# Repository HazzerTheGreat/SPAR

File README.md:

# SPAR

This is a flight controller primarily designed for fixed wing aircraft (or quadcopters etc) that is designed to 
run either BetaFlight, INAV or ArduPilot firmware. It handles flight stabilization, OSD, control of servos, waypoints,
data logging and anything else any other flight controller can do. This flight controller has an STM32H743 which is 
an extremely capable MCU with a blazing fast speed of up to 480MHz. Most likely overkill for the majority of applications
but it can accomodate for the most demanding projects. I made it as I was interested in the design of such systems
and also enjoy building aircraft and could find a highly capable flight controller useful plus the benefit that I have
built it myself.

**Specs:**

- ICM-42688-P for peak performance and high resolution positional sensing
- STM32H743 for processing whatever you need
- 5V and 9V buck converters for handling high power peripherals
- Micro SD card for black box logging
- 4 in 1 ESC support with DSHOT
- 6 other PWM outputs
- Analog OSD through AT7456E
- Support for external magnetometer, airspeed sensor and GPS
- BMP280 barometer for altitude measurements

**Peripherals:**

The flight controller board has connectors for external airspeed, GPS, and mag sensors as well as plugs for ELRS, 4 in 1 ESC, analog camera, analog VTX, digital VTX and PWM LEDs.

**Firmware/flashing:**

This board does not have custom firmware, it is based on INAV: https://github.com/iNavFlight/inav/.
However a custom build of INAV including relevant target configuration is required.
I will put this custom target in the /Project_Files/INAV folder. This tutorial shows how to build INAV with a custom target: https://youtu.be/ThrsS_y9zDo?si=cllAaaTRHZ6ADbW4
To flash the board, the board must be powered up with the boot0 pin shorted to enter DFU mode on the STM32 where it can then be flashed in INAV configurator.

**BOM:**

The board costs about £27 from JLCPCB for a basic 6 layer PCB. The BOM for components can be found in the BOM.csv in the production folder. This totals around £40 which mainly
accounts for buying large quantities of passives so the per board price is probably much cheaper.

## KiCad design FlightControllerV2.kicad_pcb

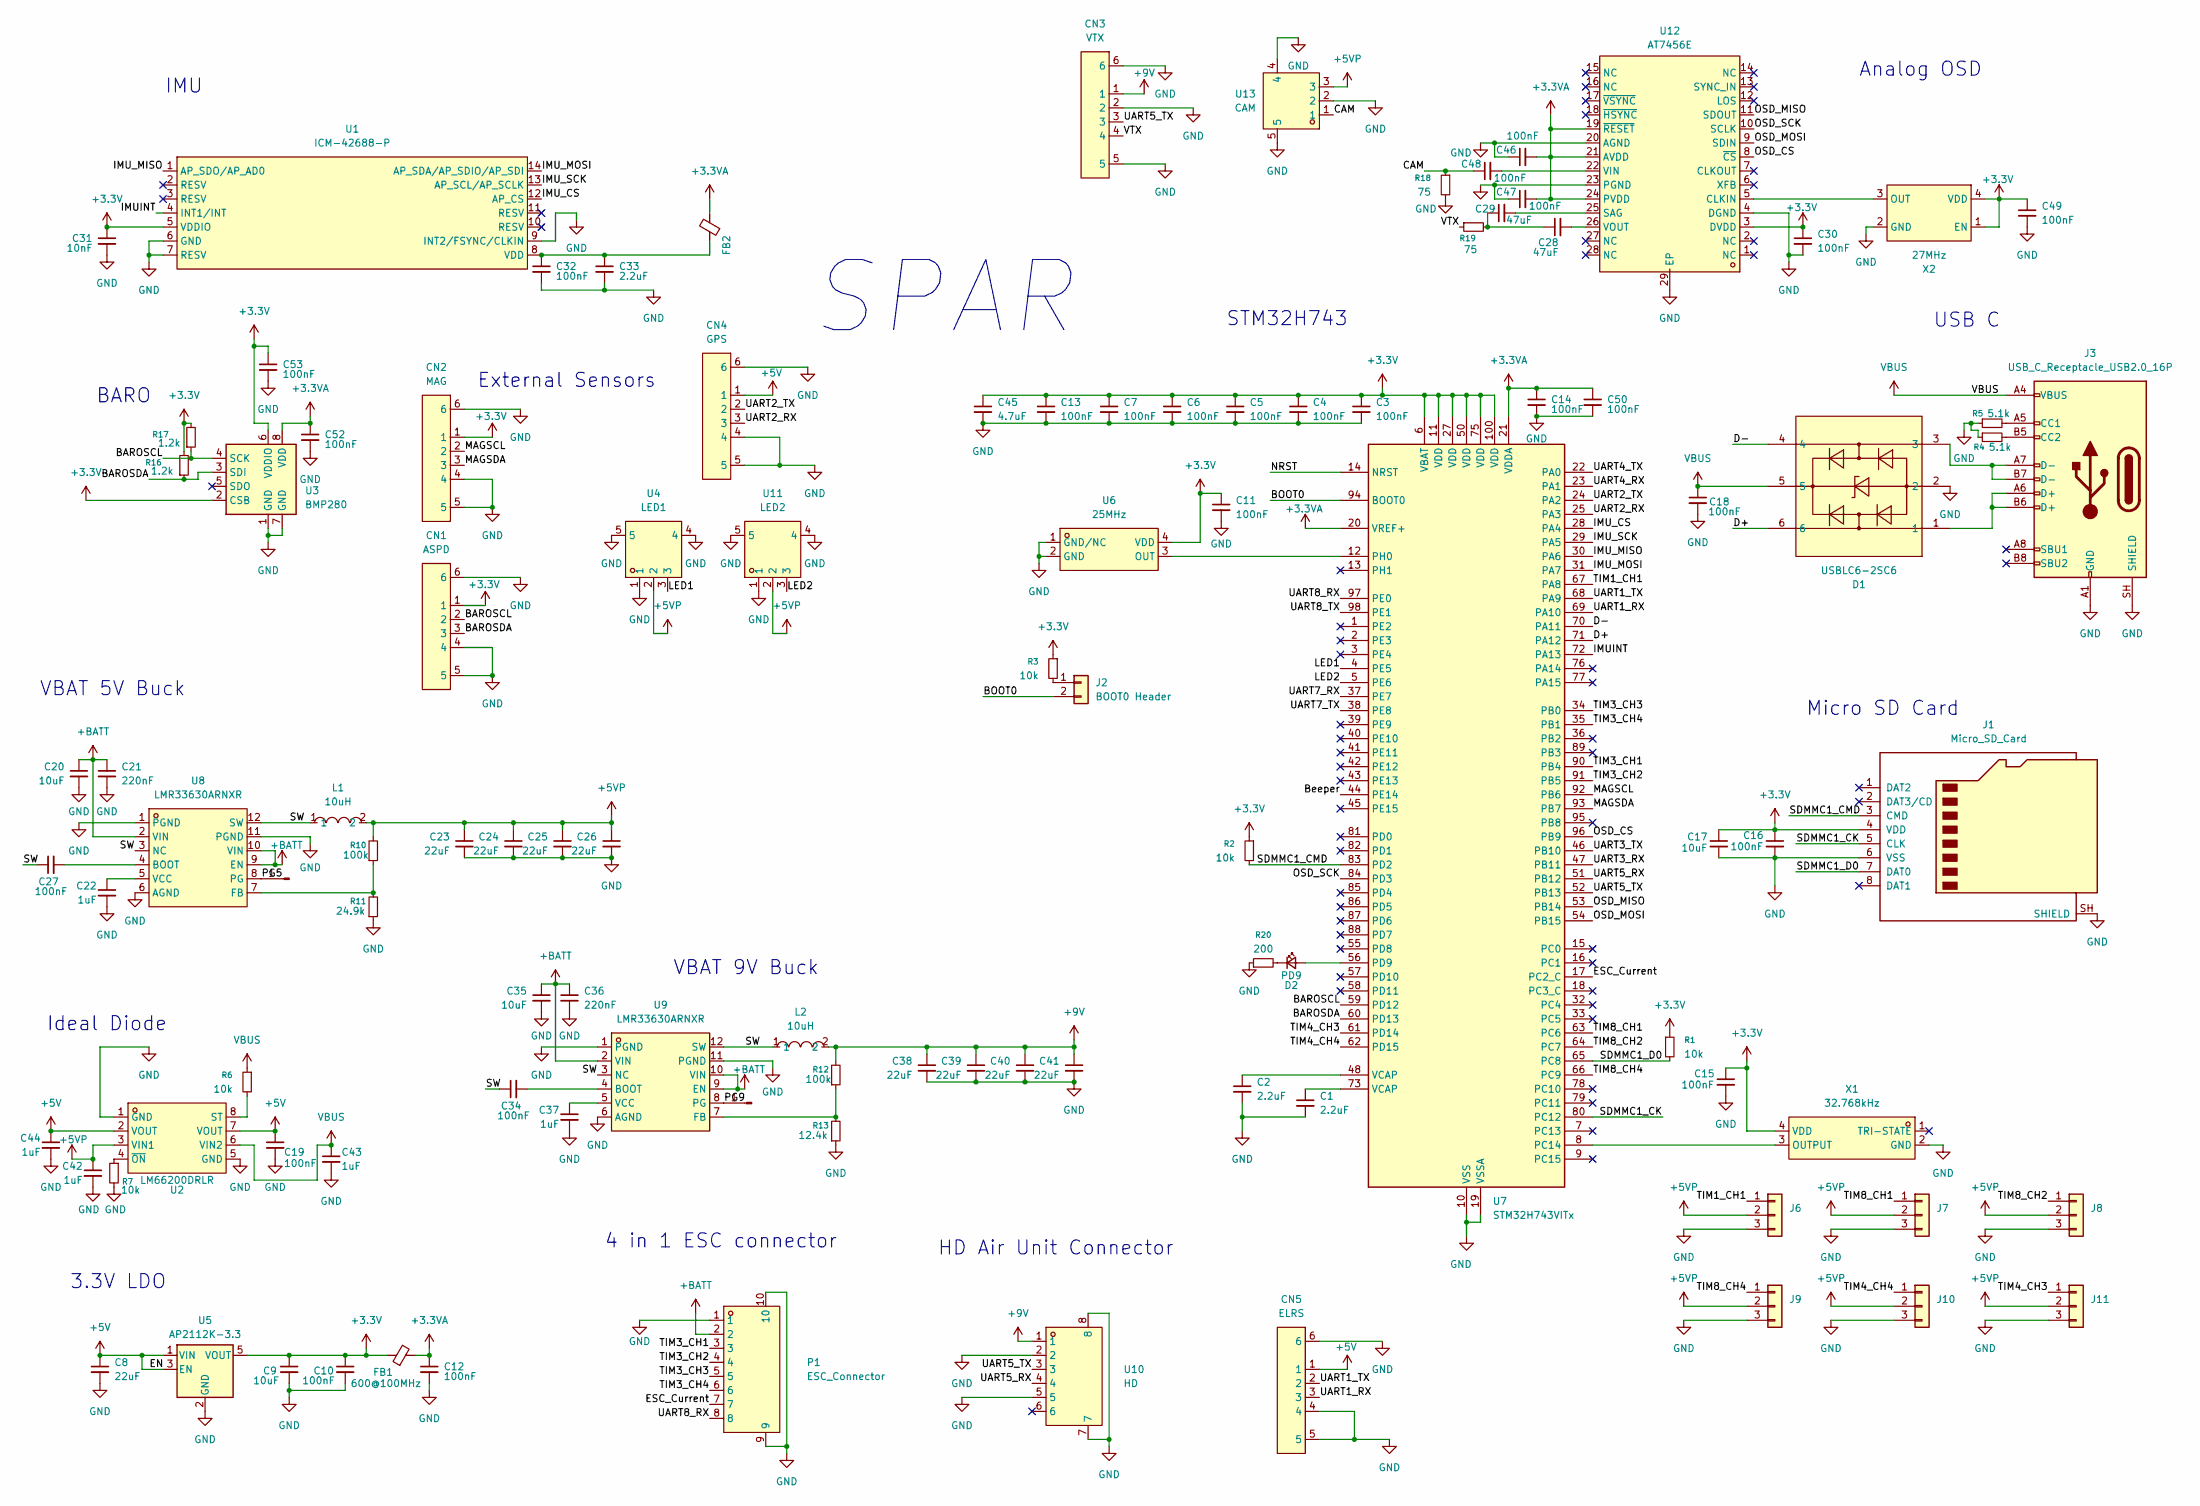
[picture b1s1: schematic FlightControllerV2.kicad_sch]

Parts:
C1, C2, C33: 2.2uF; C_0402_1005Metric
C3, C4, C5, C6, C7, C10, C11, C12, C13, C14, C15, C16, C18, C19, C27, C30, C32, C34, C46, C47, C48, C49, C50, C52, C53: 100nF; C_0402_1005Metric
C8, C23, C24, C25, C26, C38, C39, C40, C41: 22uF; C_0603_1608Metric
C9, C17, C20, C35: 10uF; C_0402_1005Metric
C21, C36: 220nF; C_0402_1005Metric
C22, C37, C42, C43, C44: 1uF; C_0402_1005Metric
C28, C29: 47uF; C_0603_1608Metric
C31: 10nF; C_0402_1005Metric
C45: 4.7uF; C_0402_1005Metric
CN1: ASPD; CONN-SMD_4P-P1.00_SM04B-SRSS-TB-LF-SN; MPN SM04B-SRSS-TB(LF)(SN); LCSC Part C160404
CN2: MAG; CONN-SMD_4P-P1.00_SM04B-SRSS-TB-LF-SN; MPN SM04B-SRSS-TB(LF)(SN); LCSC Part C160404
CN3: VTX; CONN-SMD_4P-P1.00_SM04B-SRSS-TB-LF-SN; MPN SM04B-SRSS-TB(LF)(SN); LCSC Part C160404
CN4: GPS; CONN-SMD_4P-P1.00_SM04B-SRSS-TB-LF-SN; MPN SM04B-SRSS-TB(LF)(SN); LCSC Part C160404
CN5: ELRS; CONN-SMD_4P-P1.00_SM04B-SRSS-TB-LF-SN; MPN SM04B-SRSS-TB(LF)(SN); LCSC Part C160404
D1: USBLC6-2SC6; SOT-23-6_L2.9-W1.6-P0.95-LS2.8-BL; MPN USBLC6-2SC6; LCSC Part C7519
D2: PD9; LED_0603_1608Metric
FB1, FB2: 600@100MHz; C_0603_1608Metric
J1: Micro_SD_Card; TF-SMD_TF-PUSH
J2: BOOT0 Header; PinHeader_1x02_P2.54mm_Vertical
J3: USB_C_Receptacle_USB2.0_16P; USB-C-SMD_TYPE-C-16PIN-2MD-073
J4, J5: Conn_01x01_Pin
J6, J7, J8, J9, J10, J11: Conn_01x03; PinHeader_1x03_P2.54mm_Vertical
L1, L2: 10uH; IND-SMD_L5.2-W5.2_MCW-0530; MPN SMMS0530-100M; LCSC Part C181721
P1: ESC_Connector; CONN-TH_SM08B-SRSS-TB-LF-SN; MPN SM08B-SRSS-TB(LF)(SN); LCSC Part C160407
R1, R2, R3, R6, R7: 10k; R_0603_1608Metric
R4, R5: 5.1k; R_0603_1608Metric
R10, R12: 100k; R_0603_1608Metric
R11: 24.9k; R_0603_1608Metric
R13: 12.4k; R_0603_1608Metric
R16, R17: 1.2k; R_0603_1608Metric
R18, R19: 75; R_0603_1608Metric
R20: 200; R_0603_1608Metric
U1: ICM-42688-P; LGA-14_L3.0-W2.5-P0.50-TL; MPN ICM-42688-P; LCSC Part C1850418
U2: LM66200DRLR; SOT-583-8_L2.1-W1.2-P0.50-LS1.6-BL; MPN LM66200DRLR; LCSC Part C3235556
U3: BMP280; Bosch_LGA-8_2x2.5mm_P0.65mm_ClockwisePinNumbering
U4: LED1; CONN-SMD_SM03B-SRSS-TB-LF-SN-P; MPN SM03B-SRSS-TB(LF)(SN); LCSC Part C160403
U5: AP2112K-3.3; SOT-23-5
U6: 25MHz; OSC-SMD_4P-L2.5-W2.0-BL; MPN 8122S-25.000NQ33FTL; LCSC Part C20623084
U7: STM32H743VITx; LQFP-100_14x14mm_P0.5mm
U8, U9: LMR33630ARNXR; VQFN-12_L3.0-W2.0-P0.65-BL_TI_RNX; MPN LMR33630ARNXR; LCSC Part C2861505
U10: HD; CONN-SMD_SM06B-SRSS-TB-LF-SN; MPN SM06B-SRSS-TB(LF)(SN); LCSC Part C160405
U11: LED2; CONN-SMD_SM03B-SRSS-TB-LF-SN-P; MPN SM03B-SRSS-TB(LF)(SN); LCSC Part C160403
U12: AT7456E; TSSOP-28_L9.7-W4.4-P0.65-LS6.4-BL-EP-2; MPN AT7456E; LCSC Part C82351
U13: CAM; CONN-SMD_SM03B-SRSS-TB-LF-SN-P; MPN SM03B-SRSS-TB(LF)(SN); LCSC Part C160403
X1: 32.768kHz; OSC-SMD_4P-L3.2-W2.5-BL; MPN SX3M32.768KM20F30TNN; LCSC Part C2901582
X2: 27MHz; OSC-SMD_4P-L3.2-W2.5-BL; MPN SX3M27.000M20F30TNN; LCSC Part C2901577

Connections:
+3.3V: C3.1, C4.1, C5.1, C6.1, C7.1, C9.1, C10.1, C11.1, C13.1, C15.1, C16.1, C17.1, C30.1, C31.1, C45.1, C49.1, C53.1, CN1.1, CN2.1, FB1.1, J1.4 (VDD), R1.1, R2.1, R3.1, R16.2, R17.2, U1.5 (VDDIO), U3.2 (CSB), U3.6 (VDDIO), U5.5 (VOUT), U6.4 (VDD), U7.6 (VBAT), U7.11 (VDD), U7.27 (VDD), U7.50 (VDD), U7.75 (VDD), U7.100 (VDD), U12.3 (DVDD), X1.4 (VDD), X2.1 (EN), X2.4 (VDD)
+3.3VA: C12.1, C14.1, C46.2, C47.2, C50.1, C52.1, FB1.2, FB2.2, U3.8 (VDD), U7.20 (VREF+), U7.21 (VDDA), U12.19 (~RESET), U12.21 (AVDD), U12.24 (PVDD)
+5V: C8.1, C19.1, C44.1, CN4.1, CN5.1, U2.2 (VOUT), U2.7 (VOUT), U5.1 (VIN), U5.3 (EN)
+5VP: C23.1, C24.1, C25.1, C26.1, C42.1, J6.2, J7.2, J8.2, J9.2, J10.2, J11.2, L1.2, R10.2, U2.3 (VIN1), U4.2, U11.2, U13.3
+9V: C38.1, C39.1, C40.1, C41.1, CN3.1, L2.2, R12.2, U10.1
+BATT: C20.1, C21.1, C35.1, C36.1, P1.2, U8.2 (VIN), U8.9 (EN), U8.10 (VIN), U9.2 (VIN), U9.9 (EN), U9.10 (VIN)
/BAROSCL: CN1.2, R17.1, U3.4 (SCK), U7.59 (PD12)
/BAROSDA: CN1.3, R16.1, U3.3 (SDI), U7.60 (PD13)
/BOOT0: J2.2, U7.94 (BOOT0)
/Beeper: U7.44 (PE14)
/CAM: C48.1, R18.1, U13.1
/D+: D1.6, U7.71 (PA12)
/D-: D1.4, U7.70 (PA11)
/ESC_Current: P1.7, U7.17 (PC2_C)
/IMUINT: U1.4 (INT1/INT), U7.72 (PA13)
/IMU_CS: U1.12 (AP_CS), U7.28 (PA4)
/IMU_MISO: U1.1 (AP_SDO/AP_AD0), U7.30 (PA6)
/IMU_MOSI: U1.14 (AP_SDA/AP_SDIO/AP_SDI), U7.31 (PA7)
/IMU_SCK: U1.13 (AP_SCL/AP_SCLK), U7.29 (PA5)
/LED1: U4.3, U7.4 (PE5)
/LED2: U7.5 (PE6), U11.3
/MAGSCL: CN2.2, U7.92 (PB6)
/MAGSDA: CN2.3, U7.93 (PB7)
/NRST: U7.14 (NRST)
/OSD_CS: U7.96 (PB9), U12.8 (~CS)
/OSD_MISO: U7.53 (PB14), U12.11 (SDOUT)
/OSD_MOSI: U7.54 (PB15), U12.9 (SDIN)
/OSD_SCK: U7.84 (PD3), U12.10 (SCLK)
/PG5: J4.1, U8.8 (PG)
/PG9: J5.1, U9.8 (PG)
/SDMMC1_CK: J1.5 (CLK), U7.80 (PC12)
/SDMMC1_CMD: J1.3 (CMD), R2.2, U7.83 (PD2)
/SDMMC1_D0: J1.7 (DAT0), R1.2, U7.65 (PC8)
/SW: C27.1, C34.1, L1.1, L2.1, U8.3 (NC), U8.12 (SW), U9.3 (NC), U9.12 (SW)
/TIM1_CH1: J6.1, U7.67 (PA8)
/TIM3_CH1: P1.3, U7.90 (PB4)
/TIM3_CH2: P1.4, U7.91 (PB5)
/TIM3_CH3: P1.5, U7.34 (PB0)
/TIM3_CH4: P1.6, U7.35 (PB1)
/TIM4_CH3: J11.1, U7.61 (PD14)
/TIM4_CH4: J10.1, U7.62 (PD15)
/TIM8_CH1: J7.1, U7.63 (PC6)
/TIM8_CH2: J8.1, U7.64 (PC7)
/TIM8_CH4: J9.1, U7.66 (PC9)
/UART1_RX: CN5.3, U7.69 (PA10)
/UART1_TX: CN5.2, U7.68 (PA9)
/UART2_RX: CN4.3, U7.25 (PA3)
/UART2_TX: CN4.2, U7.24 (PA2)
/UART3_RX: U7.47 (PB11)
/UART3_TX: U7.46 (PB10)
/UART4_RX: U7.23 (PA1)
/UART4_TX: U7.22 (PA0)
/UART5_RX: U7.51 (PB12), U10.4
/UART5_TX: CN3.3, U7.52 (PB13), U10.3
/UART7_RX: U7.37 (PE7)
/UART7_TX: U7.38 (PE8)
/UART8_RX: P1.8, U7.97 (PE0)
/UART8_TX: U7.98 (PE1)
/VTX: CN3.4, R19.1
GND: C1.2, C2.2, C3.2, C4.2, C5.2, C6.2, C7.2, C8.2, C9.2, C10.2, C11.2, C12.2, C13.2, C14.2, C15.2, C16.2, C17.2, C18.2, C19.2, C20.2, C21.2, C22.2, C23.2, C24.2, C25.2, C26.2, C30.2, C31.2, C32.2, C33.2, C35.2, C36.2, C37.2, C38.2, C39.2, C40.2, C41.2, C42.2, C43.2, C44.2, C45.2, C46.1, C47.1, C49.2, C50.2, C52.2, C53.2, CN1.4, CN1.5, CN1.6, CN2.4, CN2.5, CN2.6, CN3.2, CN3.5, CN3.6, CN4.4, CN4.5, CN4.6, CN5.4, CN5.5, CN5.6, D1.2, J1.6 (VSS), J1.SH (SHIELD), J3.13, J3.14, J3.A1 (GND), J3.A1B12, J3.A12 (GND), J3.B1 (GND), J3.B1A12, J3.B12 (GND), J3.SH (SHIELD), J6.3, J7.3, J8.3, J9.3, J10.3, J11.3, P1.1, P1.9, P1.10, R4.1, R5.1, R7.2, R11.1, R13.1, R18.2, R20.1, U1.6 (GND), U1.7 (RESV), U1.9 (INT2/FSYNC/CLKIN), U2.1 (GND), U2.5 (GND), U3.1 (GND), U3.7 (GND), U4.1, U4.4, U4.5, U5.2 (GND), U6.1 (GND/NC), U6.2 (GND), U7.10 (VSS), U7.19 (VSSA), U7.26 (VSS), U7.49 (VSS), U7.74 (VSS), U7.99 (VSS), U8.1 (PGND), U8.6 (AGND), U8.11 (PGND), U9.1 (PGND), U9.6 (AGND), U9.11 (PGND), U10.2, U10.5, U10.7, U10.8, U11.1, U11.4, U11.5, U12.4 (DGND), U12.20 (AGND), U12.23 (PGND), U12.29 (EP), U13.2, U13.4, U13.5, X1.2 (GND), X2.2 (GND)
unnamed: C1.1, U7.73 (VCAP)
unnamed: C2.1, U7.48 (VCAP)
unnamed: C28.1, C29.1, R19.2
unnamed: D1.1, J3.A6 (D+), J3.B6 (D+)
unnamed: D1.3, J3.A7 (D-), J3.B7 (D-)
unnamed: D2.2 (A), U7.56 (PD9)
unnamed: D2.1 (K), R20.2
unnamed: J2.1, R3.2
unnamed: J3.A5 (CC1), R5.2
unnamed: J3.B5 (CC2), R4.2
unnamed: C32.1, C33.1, FB2.1, U1.8 (VDD)
unnamed: R6.2, U2.8 (ST)
unnamed: R7.1, U2.4 (~ON)
unnamed: U6.3 (OUT), U7.12 (PH0)
unnamed: U7.8 (PC14), X1.3 (OUTPUT)
unnamed: C27.2, U8.4 (BOOT)
unnamed: R10.1, R11.2, U8.7 (FB)
unnamed: C22.1, U8.5 (VCC)
unnamed: C34.2, U9.4 (BOOT)
unnamed: R12.1, R13.2, U9.7 (FB)
unnamed: C37.1, U9.5 (VCC)
unnamed: U12.5 (CLKIN), X2.3 (OUT)
unnamed: C29.2, U12.25 (SAG)
unnamed: C48.2, U12.22 (VIN)
unnamed: C28.2, U12.26 (VOUT)
VBUS: C18.1, C43.1, D1.5, J3.A4 (VBUS), J3.A9 (VBUS), J3.B4 (VBUS), J3.B9 (VBUS), R6.1, U2.6 (VIN2)

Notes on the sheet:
External Sensors
Analog OSD
BARO
Ideal Diode
SPAR
VBAT 5V Buck
VBAT 9V Buck
Micro SD Card
4 in 1 ESC connector
IMU
3.3V LDO
STM32H743
USB C
HD Air Unit Connector

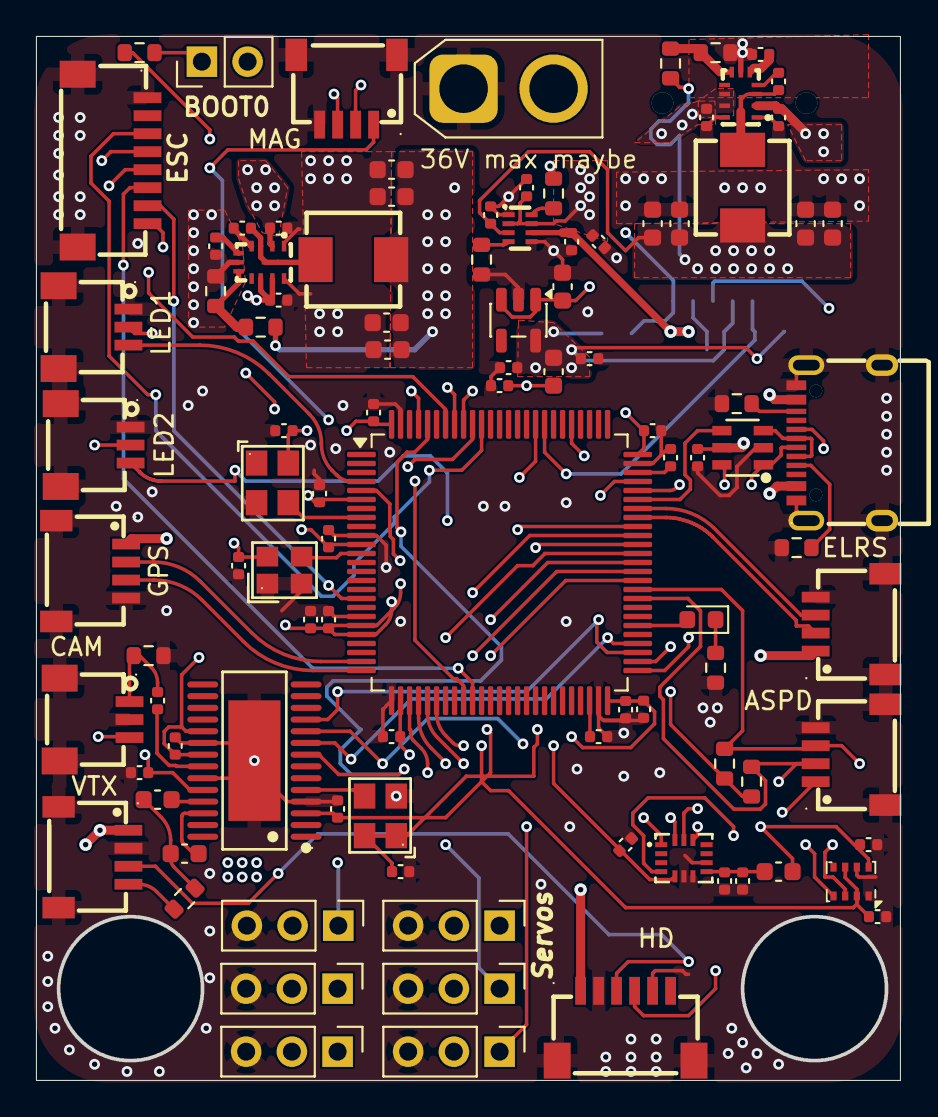
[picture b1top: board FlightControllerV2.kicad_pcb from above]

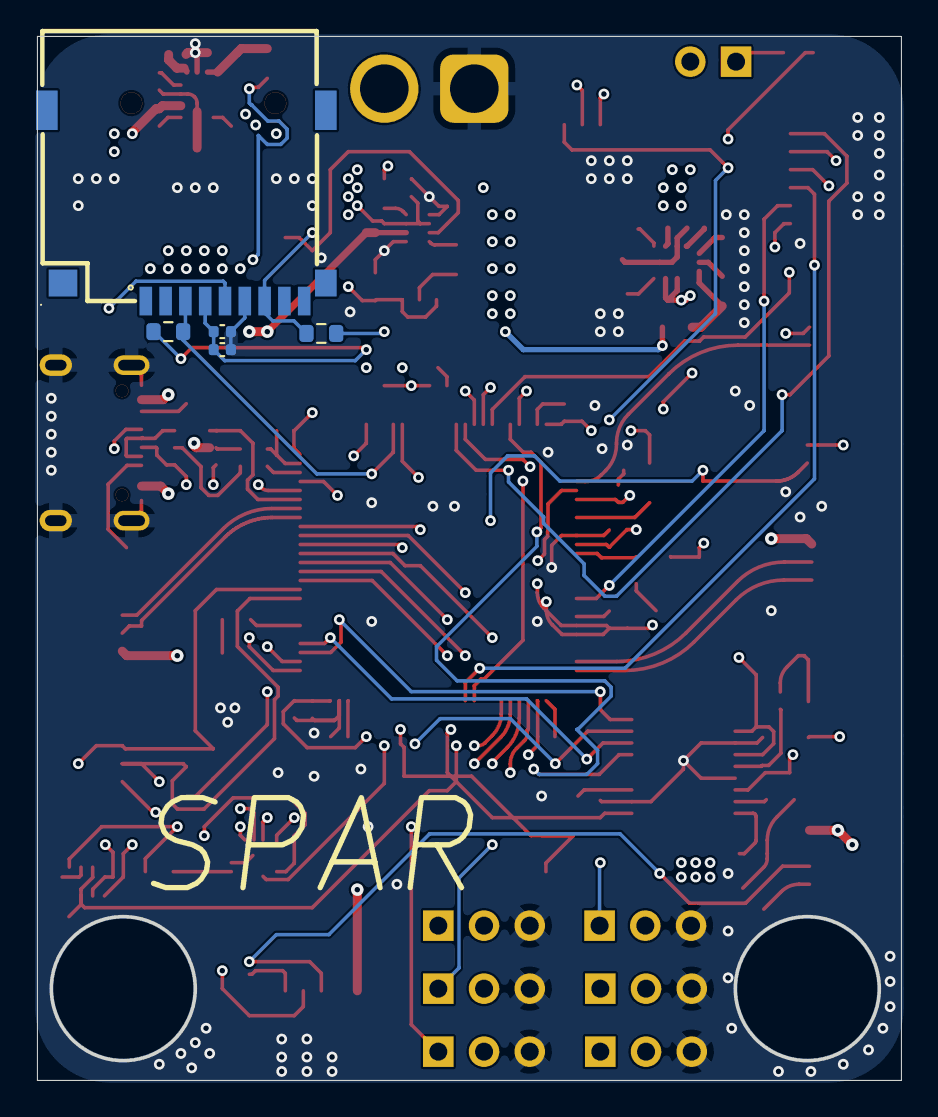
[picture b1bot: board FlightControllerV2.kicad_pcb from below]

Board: 6 copper layers, 48.0 x 58.0 mm, 104 parts (5 on the bottom side), 75 nets.

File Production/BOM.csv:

Reference,Qty,Value,DNP,Exclude from BOM,Exclude from Board,Exclude from Simulation,Exclude from Position Files,Footprint,Datasheet,,,,,,,Price (minimum order):,
"C1,C2,C33",3,2.2uF,,,,,${EXCLUDE_FROM_POS_FILES},Capacitor_SMD:C_0402_1005Metric,,,,,,,,,0.45
"C3,C4,C5,C6,C7,C10,C11,C12,C13,C14,C15,C16,C18,C19,C27,C30,C32,C34,C46,C47,C48,C49,C50,C52,C53",25,100nF,,,,,${EXCLUDE_FROM_POS_FILES},Capacitor_SMD:C_0402_1005Metric,,,,,,,,,0.45
"C8,C23,C24,C25,C26,C38,C39,C40,C41",9,22uF,,,,,${EXCLUDE_FROM_POS_FILES},Capacitor_SMD:C_0603_1608Metric,,,,,,,,,0.45
"C9,C17,C20,C35",4,10uF,,,,,${EXCLUDE_FROM_POS_FILES},Capacitor_SMD:C_0402_1005Metric,,,,,,,,,0.45
"C21,C36",2,220nF,,,,,${EXCLUDE_FROM_POS_FILES},Capacitor_SMD:C_0402_1005Metric,,,,,,,,,0.45
"C22,C37,C42,C43,C44",5,1uF,,,,,${EXCLUDE_FROM_POS_FILES},Capacitor_SMD:C_0402_1005Metric,,,,,,,,,0.45
"C28,C29",2,47uF,,,,,${EXCLUDE_FROM_POS_FILES},Capacitor_SMD:C_0603_1608Metric,,,,,,,,,0.97
C31,1,10nF,,,,,${EXCLUDE_FROM_POS_FILES},Capacitor_SMD:C_0402_1005Metric,,,,,,,,,0.45
C45,1,4.7uF,,,,,${EXCLUDE_FROM_POS_FILES},Capacitor_SMD:C_0402_1005Metric,,,,,,,,,0.45
CN1,1,ASPD,,,,,${EXCLUDE_FROM_POS_FILES},easyeda2kicad:CONN-SMD_4P-P1.00_SM04B-SRSS-TB-LF-SN,https://lcsc.com/product-detail/Others_JST-Sales-America__JS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,,,,,,,,0.18
CN2,1,MAG,,,,,${EXCLUDE_FROM_POS_FILES},easyeda2kicad:CONN-SMD_4P-P1.00_SM04B-SRSS-TB-LF-SN,https://lcsc.com/product-detail/Others_JST-Sales-America__JS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,,,,,,,,0.19
CN3,1,VTX,,,,,${EXCLUDE_FROM_POS_FILES},easyeda2kicad:CONN-SMD_4P-P1.00_SM04B-SRSS-TB-LF-SN,https://lcsc.com/product-detail/Others_JST-Sales-America__JS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,,,,,,,,0.18
CN4,1,GPS,,,,,${EXCLUDE_FROM_POS_FILES},easyeda2kicad:CONN-SMD_4P-P1.00_SM04B-SRSS-TB-LF-SN,https://lcsc.com/product-detail/Others_JST-Sales-America__JS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,,,,,,,,0.18
CN5,1,ELRS,,,,,${EXCLUDE_FROM_POS_FILES},easyeda2kicad:CONN-SMD_4P-P1.00_SM04B-SRSS-TB-LF-SN,https://lcsc.com/product-detail/Others_JST-Sales-America__JS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,,,,,,,,0.18
D1,1,USBLC6-2SC6,,,,,${EXCLUDE_FROM_POS_FILES},easyeda2kicad:SOT-23-6_L2.9-W1.6-P0.95-LS2.8-BL,https://lcsc.com/product-detail/Diodes-ESD_STMicroelectronic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,,,,,,,,0.82
D2,1,PD9,,,,,${EXCLUDE_FROM_POS_FILES},LED_SMD:LED_0603_1608Metric,,,,,,,,,0.78
"FB1,FB2",2,600@100MHz,,,,,${EXCLUDE_FROM_POS_FILES},Capacitor_SMD:C_0603_1608Metric,,,,,,,,,0.79
J1,1,Micro_SD_Card,,,,,${EXCLUDE_FROM_POS_FILES},easyeda2kicad:TF-SMD_TF-PUSH,https://www.we-online.com/components/products/datasheet/6930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,,,,,,,,0.56
J2,1,BOOT0 Header,,,,,${EXCLUDE_FROM_POS_FILES},Connector_PinHeader_2.54mm:PinHeader_1x02_P2.54mm_Vertical,,,,,,,,,0.12
J3,1,USB_C_Receptacle_USB2.0_16P,,,,,${EXCLUDE_FROM_POS_FILES},easyeda2kicad:USB-C-SMD_TYPE-C-16PIN-2MD-073,https://www.usb.org/sites/default/files/documents/usb_type-c.zip,,,,,,,,1.27
"J4,J5",2,Conn_01x01_Pin,,,,,${EXCLUDE_FROM_POS_FILES},,,,,,,,,,0.2
"J6,J7,J8,J9,J10,J11",6,Conn_01x03,,,,,${EXCLUDE_FROM_POS_FILES},Connector_PinHeader_2.54mm:PinHeader_1x03_P2.54mm_Vertical,,,,,,,,,0.8
"L1,L2",2,10uH,,,,,${EXCLUDE_FROM_POS_FILES},easyeda2kicad:IND-SMD_L5.2-W5.2_MCW-0530,https://lcsc.com/product-detail/Power-Inductors_10uH-20_C181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,,,,,,,,0.7
P1,1,ESC_Connector,,,,,${EXCLUDE_FROM_POS_FILES},easyeda2kicad:CONN-TH_SM08B-SRSS-TB-LF-SN,https://lcsc.com/product-detail/Others_JST-Sales-America__JS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,,,,,,,,0.55
"R1,R2,R3,R6,R7",5,10k,,,,,${EXCLUDE_FROM_POS_FILES},Resistor_SMD:R_0603_1608Metric,,,,,,,,,0.45
"R4,R5",2,5.1k,,,,,${EXCLUDE_FROM_POS_FILES},Resistor_SMD:R_0603_1608Metric,,,,,,,,,0.45
"R10,R12",2,100k,,,,,${EXCLUDE_FROM_POS_FILES},Resistor_SMD:R_0603_1608Metric,,,,,,,,,0.45
R11,1,24.9k,,,,,${EXCLUDE_FROM_POS_FILES},Resistor_SMD:R_0603_1608Metric,,,,,,,,,0.45
R13,1,12.4k,,,,,${EXCLUDE_FROM_POS_FILES},Resistor_SMD:R_0603_1608Metric,,,,,,,,,0.45
"R16,R17",2,1.2k,,,,,${EXCLUDE_FROM_POS_FILES},Resistor_SMD:R_0603_1608Metric,,,,,,,,,0.45
"R18,R19",2,75,,,,,${EXCLUDE_FROM_POS_FILES},Resistor_SMD:R_0603_1608Metric,,,,,,,,,0.45
R20,1,200,,,,,${EXCLUDE_FROM_POS_FILES},Resistor_SMD:R_0603_1608Metric,,,,,,,,,0.45
U1,1,ICM-42688-P,,,,,${EXCLUDE_FROM_POS_FILES},easyeda2kicad:LGA-14_L3.0-W2.5-P0.50-TL,https://www.lcsc.com/datasheet/C1850418.pdf,,,,,,,,6.29
U2,1,LM66200DRLR,,,,,${EXCLUDE_FROM_POS_FILES},easyeda2kicad:SOT-583-8_L2.1-W1.2-P0.50-LS1.6-BL,https://www.lcsc.com/datasheet/C3235556.pdf,,,,,,,,0.53
U3,1,BMP280,,,,,${EXCLUDE_FROM_POS_FILES},Package_LGA:Bosch_LGA-8_2x2.5mm_P0.65mm_ClockwisePinNumbering,https://ae-bst.resource.bosch.com/media/_tech/media/datashee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,,,,,,,,1
U4,1,LED1,,,,,${EXCLUDE_FROM_POS_FILES},easyeda2kicad:CONN-SMD_SM03B-SRSS-TB-LF-SN-P,https://lcsc.com/product-detail/Others_JST-Sales-America__JS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,,,,,,,,0.33
U5,1,AP2112K-3.3,,,,,${EXCLUDE_FROM_POS_FILES},Package_TO_SOT_SMD:SOT-23-5,https://www.diodes.com/assets/Datasheets/AP2112.pdf,,,,,,,,0.24
U6,1,25MHz,,,,,${EXCLUDE_FROM_POS_FILES},easyeda2kicad:OSC-SMD_4P-L2.5-W2.0-BL,https://www.lcsc.com/datasheet/C20623084.pdf,,,,,,,,0.52
U7,1,STM32H743VITx,,,,,${EXCLUDE_FROM_POS_FILES},Package_QFP:LQFP-100_14x14mm_P0.5mm,https://www.st.com/resource/en/datasheet/stm32h743vi.pdf,,,,,,,,10.71
"U8,U9",2,LMR33630ARNXR,,,,,${EXCLUDE_FROM_POS_FILES},easyeda2kicad:VQFN-12_L3.0-W2.0-P0.65-BL_TI_RNX,https://www.lcsc.com/datasheet/C2861505.pdf,,,,,,,,3.64
U10,1,HD,,,,,${EXCLUDE_FROM_POS_FILES},easyeda2kicad:CONN-SMD_SM06B-SRSS-TB-LF-SN,https://lcsc.com/product-detail/Others_JST-Sales-America__JS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,,,,,,,,0.7
U11,1,LED2,,,,,${EXCLUDE_FROM_POS_FILES},easyeda2kicad:CONN-SMD_SM03B-SRSS-TB-LF-SN-P,https://lcsc.com/product-detail/Others_JST-Sales-America__JS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,,,,,,,,0.6
U12,1,AT7456E,,,,,${EXCLUDE_FROM_POS_FILES},easyeda2kicad:TSSOP-28_L9.7-W4.4-P0.65-LS6.4-BL-EP-2,https://lcsc.com/product-detail/Analog-ICs_AT7456E_C82351.html,,,,,,,,3.32
U13,1,CAM,,,,,${EXCLUDE_FROM_POS_FILES},easyeda2kicad:CONN-SMD_SM03B-SRSS-TB-LF-SN-P,https://lcsc.com/product-detail/Others_JST-Sales-America__JS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,,,,,,,,0.6
X1,1,32.768kHz,,,,,${EXCLUDE_FROM_POS_FILES},easyeda2kicad:OSC-SMD_4P-L3.2-W2.5-BL,https://www.lcsc.com/datasheet/C2901582.pdf,,,,,,,,0.55
X2,1,27MHz,,,,,${EXCLUDE_FROM_POS_FILES},easyeda2kicad:OSC-SMD_4P-L3.2-W2.5-BL,https://www.lcsc.com/datasheet/C2901577.pdf,,,,,,,,0.76

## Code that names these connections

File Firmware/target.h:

/*
 * This file is part of INAV.
 *
 * INAV is free software: you can redistribute it and/or modify
 * it under the terms of the GNU General Public License as published by
 * the Free Software Foundation, either version 3 of the License, or
 * (at your option) any later version.
 *
 * INAV is distributed in the hope that it will be useful,
 * but WITHOUT ANY WARRANTY; without even the implied warranty of
 * MERCHANTABILITY or FITNESS FOR A PARTICULAR PURPOSE.  See the
 * GNU General Public License for more details.
 *
 * You should have received a copy of the GNU General Public License
 * along with INAV.  If not, see <http://www.gnu.org/licenses/>.
 */


#pragma once

#define TARGET_BOARD_IDENTIFIER "H743"


#define USBD_PRODUCT_STRING     "SPARH743"


#define USE_TARGET_CONFIG

#define LED0                    PE5
#define LED1                    PE6


// *************** IMU generic ***********************
#define USE_TARGET_IMU_HARDWARE_DESCRIPTORS



// *************** SPI1 IMU0 MPU6000 ****************
#define USE_SPI
#define USE_SPI_DEVICE_1
#define SPI1_SCK_PIN            PA5
#define SPI1_MISO_PIN           PA6
#define SPI1_MOSI_PIN           PD7

#define USE_IMU_MPU6000

#define IMU_MPU6000_ALIGN       CW0_DEG_FLIP
#define MPU6000_SPI_BUS          BUS_SPI1
#define MPU6000_CS_PIN          PC15


// *************** SPI2 OSD ***********************
  #define USE_SPI_DEVICE_2
  #define SPI2_SCK_PIN            PB13
  #define SPI2_MISO_PIN           PB14
  #define SPI2_MOSI_PIN           PB15

#if defined(MATEKH743)
  #define USE_MAX7456
  #define MAX7456_SPI_BUS         BUS_SPI2
  #define MAX7456_CS_PIN          PB12
#endif

// *************** I2C /Baro/Mag *********************
#define USE_I2C
#define USE_I2C_DEVICE_1
#define I2C1_SCL                PB6
#define I2C1_SDA                PB7

#define USE_I2C_DEVICE_2
#define I2C2_SCL                PB10
#define I2C2_SDA                PB11

#define USE_BARO
#define BARO_I2C_BUS            BUS_I2C2
#define USE_BARO_BMP280
#define USE_BARO_MS5611
#define USE_BARO_DPS310
#define USE_BARO_SPL06

#define USE_MAG
#define MAG_I2C_BUS             BUS_I2C1
#define USE_MAG_ALL

#define TEMPERATURE_I2C_BUS     BUS_I2C2
#define PITOT_I2C_BUS           BUS_I2C2

#define USE_RANGEFINDER
#define RANGEFINDER_I2C_BUS     BUS_I2C1

// *************** UART *****************************
#define USE_VCP

#define USE_UART1
#define UART1_TX_PIN            PA9
#define UART1_RX_PIN            PA10

#define USE_UART2
#define UART2_TX_PIN            PD5
#define UART2_RX_PIN            PD6

#define USE_UART3
#define UART3_TX_PIN            PD8
#define UART3_RX_PIN            PD9

#define USE_UART4
#define UART4_TX_PIN            PB9
#define UART4_RX_PIN            PB8

#define USE_UART6
#define UART6_TX_PIN            PC6
#define UART6_RX_PIN            PC7

#define USE_UART7
#define UART7_TX_PIN            PE8
#define UART7_RX_PIN            PE7

#define USE_UART8
#define UART8_TX_PIN            PE1
#define UART8_RX_PIN            PE0

#define USE_SOFTSERIAL1
#define SOFTSERIAL_1_TX_PIN      PC6  //TX6 pad
#define SOFTSERIAL_1_RX_PIN      PC6  //TX6 pad

#define SERIAL_PORT_COUNT       9

#define DEFAULT_RX_TYPE         RX_TYPE_SERIAL
#define SERIALRX_PROVIDER       SERIALRX_CRSF
#define SERIALRX_UART           SERIAL_PORT_USART6

// *************** SDIO SD BLACKBOX*******************
#define USE_SDCARD
#define USE_SDCARD_SDIO
#define SDCARD_SDIO_DEVICE      SDIODEV_1
#define SDCARD_SDIO_4BIT

#define ENABLE_BLACKBOX_LOGGING_ON_SDCARD_BY_DEFAULT

// *************** ADC *****************************
#define USE_ADC
#define ADC_INSTANCE                ADC1

#define ADC_CHANNEL_1_PIN           PC0  //ADC123 VBAT1
#define ADC_CHANNEL_2_PIN           PC1  //ADC123 CURR1
#define ADC_CHANNEL_3_PIN           PC5  //ADC12  RSSI
#define ADC_CHANNEL_4_PIN           PC4  //ADC12  AirS
#define ADC_CHANNEL_5_PIN           PA4  //ADC12  VB2
#define ADC_CHANNEL_6_PIN           PA7  //ADC12  CU2

#define VBAT_ADC_CHANNEL            ADC_CHN_1
#define CURRENT_METER_ADC_CHANNEL   ADC_CHN_2
#define RSSI_ADC_CHANNEL            ADC_CHN_3
#define AIRSPEED_ADC_CHANNEL        ADC_CHN_4

// *************** PINIO ***************************
#define USE_PINIO
#define USE_PINIOBOX
#define PINIO1_PIN                  PD10  // VTX power switcher
#define PINIO2_PIN                  PD11  // 2xCamera switcher

// *************** LEDSTRIP ************************
#define USE_LED_STRIP
#define WS2811_PIN                  PA8

#define DEFAULT_FEATURES            (FEATURE_OSD | FEATURE_TELEMETRY | FEATURE_CURRENT_METER | FEATURE_VBAT | FEATURE_TX_PROF_SEL | FEATURE_BLACKBOX)
#define CURRENT_METER_SCALE         250

#define USE_SERIAL_4WAY_BLHELI_INTERFACE

#define TARGET_IO_PORTA (0xffff & ~(BIT(14) | BIT(13)))
#define TARGET_IO_PORTB 0xffff
#define TARGET_IO_PORTC 0xffff
#define TARGET_IO_PORTD 0xffff
#define TARGET_IO_PORTE 0xffff

#define MAX_PWM_OUTPUT_PORTS        15
#define USE_DSHOT
#define USE_ESC_SENSOR

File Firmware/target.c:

/*
 * This file is part of INAV.
 *
 * INAV is free software: you can redistribute it and/or modify
 * it under the terms of the GNU General Public License as published by
 * the Free Software Foundation, either version 3 of the License, or
 * (at your option) any later version.
 *
 * INAV is distributed in the hope that it will be useful,
 * but WITHOUT ANY WARRANTY; without even the implied warranty of
 * MERCHANTABILITY or FITNESS FOR A PARTICULAR PURPOSE.  See the
 * GNU General Public License for more details.
 *
 * You should have received a copy of the GNU General Public License
 * along with INAV.  If not, see <http://www.gnu.org/licenses/>.
 */

#include <stdint.h>

#include "platform.h"

#include "drivers/bus.h"
#include "drivers/io.h"
#include "drivers/pwm_mapping.h"
#include "drivers/timer.h"
#include "drivers/pinio.h"
#include "drivers/sensor.h"

BUSDEV_REGISTER_SPI_TAG(busdev_mpu6000,  DEVHW_MPU6000,  MPU6000_SPI_BUS,   MPU6000_CS_PIN,   NONE,   0,  DEVFLAGS_NONE,  IMU_MPU6000_ALIGN);
BUSDEV_REGISTER_SPI_TAG(busdev_icm42688, DEVHW_ICM42605, MPU6000_SPI_BUS,   MPU6000_CS_PIN,   NONE,   0,  DEVFLAGS_NONE,  IMU_MPU6000_ALIGN);
BUSDEV_REGISTER_SPI_TAG(busdev_icm20602, DEVHW_MPU6500,  MPU6500_SPI_BUS,   MPU6500_CS_PIN,   NONE,   1,  DEVFLAGS_NONE,  IMU_MPU6500_ALIGN);
BUSDEV_REGISTER_SPI_TAG(busdev_icm42605, DEVHW_ICM42605, ICM42605_SPI_BUS,  ICM42605_CS_PIN,  NONE,  2,  DEVFLAGS_NONE,  IMU_ICM42605_ALIGN);

timerHardware_t timerHardware[] = {
    DEF_TIM(TIM3, CH1, PB4, TIM_USE_OUTPUT_AUTO, 0, 0),   // S1
    DEF_TIM(TIM3, CH2, PB5, TIM_USE_OUTPUT_AUTO, 0, 1),   // S2

    DEF_TIM(TIM3, CH3, PB0, TIM_USE_OUTPUT_AUTO, 0, 2),   // S3  
    DEF_TIM(TIM3, CH4, PB1, TIM_USE_OUTPUT_AUTO, 0, 3),   // S4
    DEF_TIM(TIM1, CH1, PA8, TIM_USE_OUTPUT_AUTO, 0, 4),   // S5
    DEF_TIM(TIM4, CH3, PD14, TIM_USE_OUTPUT_AUTO, 0, 5),   // S6

    DEF_TIM(TIM4, CH4, PD15, TIM_USE_OUTPUT_AUTO, 0, 6),   // S7
    DEF_TIM(TIM8, CH1, PC6, TIM_USE_OUTPUT_AUTO, 0, 7),   // S8
    DEF_TIM(TIM8, CH2, PC7, TIM_USE_OUTPUT_AUTO, 0, 9),   // S9
    DEF_TIM(TIM8, CH4, PC9, TIM_USE_OUTPUT_AUTO, 0, 10),   // S10 

    DEF_TIM(TIM15,  CH1, PE5,  TIM_USE_LED, 0, 9),    // LED_2812
    DEF_TIM(TIM15,  CH2, PE6,  TIM_USE_LED, 0, 9),    // LED_2812
};

const int timerHardwareCount = sizeof(timerHardware) / sizeof(timerHardware[0]);
